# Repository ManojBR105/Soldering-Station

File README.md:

# Soldering-Station
Board and Schematics for Soldering station based on hakko 907 clone. 
Consider there is slight difference in schematic, the buzzer is connected to pin no.D13 of the arduino and the lcd pin connected to the D13th pin is connected to the D11th pin of the arduino. (please change this in the arduino code before uploading OR use the modified code in this repository).
In this layout LCD and Encoder are not on the PCB but are connected using Jumper Connectors which makes the assembling job easier when mounting this circuit into a Project case.
The eagle libraries that I have used for this schematic are also with this files copy them to your eagle library.
THANK YOU.

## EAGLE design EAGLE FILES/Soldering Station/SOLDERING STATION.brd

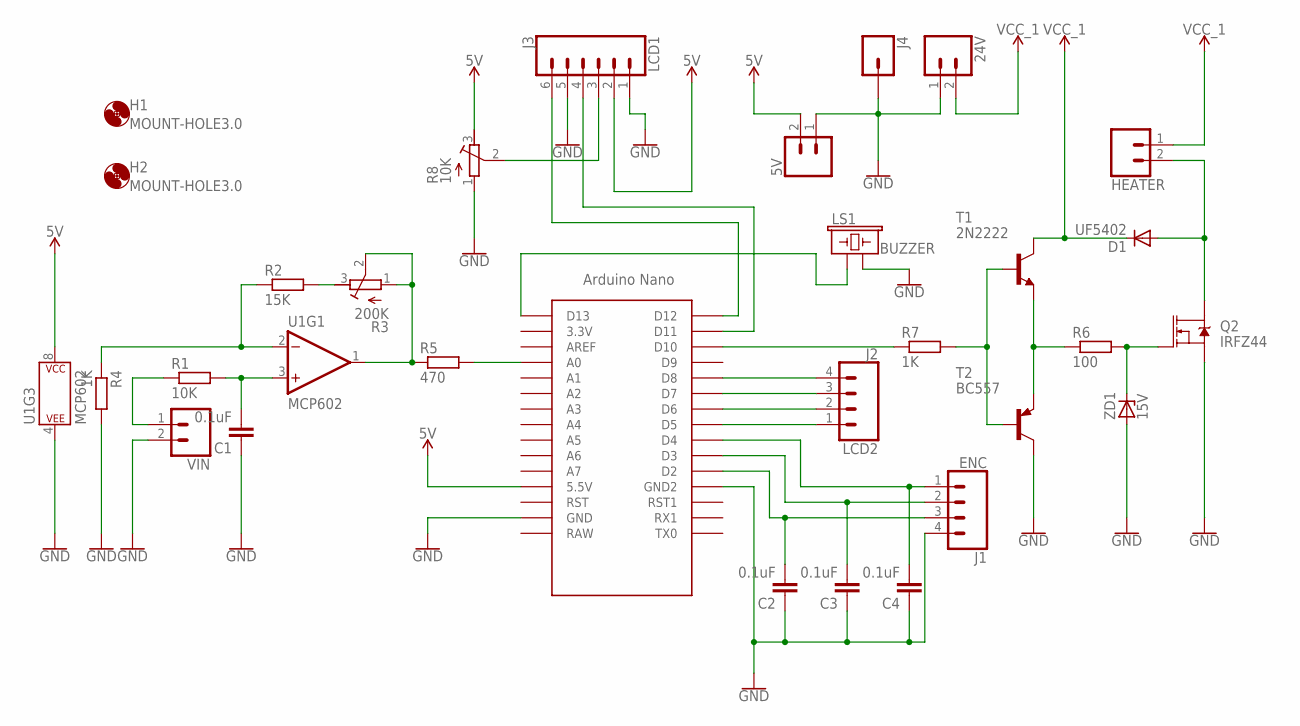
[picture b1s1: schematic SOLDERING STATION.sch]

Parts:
5V, 24V: CONN_025MM; SCREWTERMINAL-5MM-2
C1, C2, C3, C4: 0.1uF; C025-024X044
D1: UF5402; DO41-10
H1, H2: MOUNT-HOLE3.0; 3,0
HEATER: CONN_02PTH4; 1X02_XTRA_BIG
J1: ENC; 1X04_LONGPADS
J2: LCD2; 1X04_LONGPADS
J3: LCD1; 1X06_LONGPADS
J4: CONN_01PTH_2MM; 1X01_2MM
LS1: BUZZER; BUZZER-12MM-NS
Q2: IRFZ44; TO220V
R1: 10K; 0204/7
R2: 15K; 0204/7
R3: 200K; RTRIM64W
R4, R7: 1K; 0204/7
R5: 470; 0204/7
R6: 100; 0204/7
R8: 10K; RTRIM64W
T1: 2N2222; TO92-EBC-OVAL
T2: BC557; TO92
U1: MCP602; DIP08
U$1: NANO
VIN: CONN_02POLAR_LOCK; MOLEX-1X2_LOCK
ZD1: 15V; DO41Z10

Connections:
5V: 5V.2, J3.2, R8.3 (E), U1.8 (P$V+), U$1.5V (5.5V)
GND: 5V.1, 24V.1, C1.1, C2.1, C3.1, C4.1, J1.4, J3.1, J3.5, J4.1, LS1.- (2), Q2.3 (S), R4.2, R8.1 (A), T2.3 (C), U1.4 (P$V-), U$1.GND, U$1.GND1 (GND2), VIN.2, ZD1.A
unnamed: C1.2, R1.2, U1.3 (+IN)
unnamed: R2.1, R4.1, U1.2 (-IN)
unnamed: R1.1, VIN.1
unnamed: R2.2, R3.3 (E)
unnamed: R3.1 (A), R3.2 (S), R5.1, U1.1 (OUT)
unnamed: R5.2, U$1.A0
unnamed: R7.1, U$1.D10
unnamed: D1.A, HEATER.2, Q2.2 (D)
unnamed: C4.2, J1.1, U$1.D4
unnamed: R7.2, T1.B, T2.2 (B)
unnamed: R6.1, T1.E, T2.1 (E)
unnamed: Q2.1 (G), R6.2, ZD1.C
unnamed: C3.2, J1.2, U$1.D3
unnamed: C2.2, J1.3, U$1.D2
unnamed: J2.1, U$1.D5
unnamed: J2.2, U$1.D6
unnamed: J3.3, R8.2 (S)
unnamed: J2.3, U$1.D7
unnamed: J2.4, U$1.D8
unnamed: LS1.+ (1), U$1.D13
unnamed: J3.6, U$1.D12
unnamed: J3.4, U$1.D11
VCC_1: 24V.2, D1.C, HEATER.1, T1.C

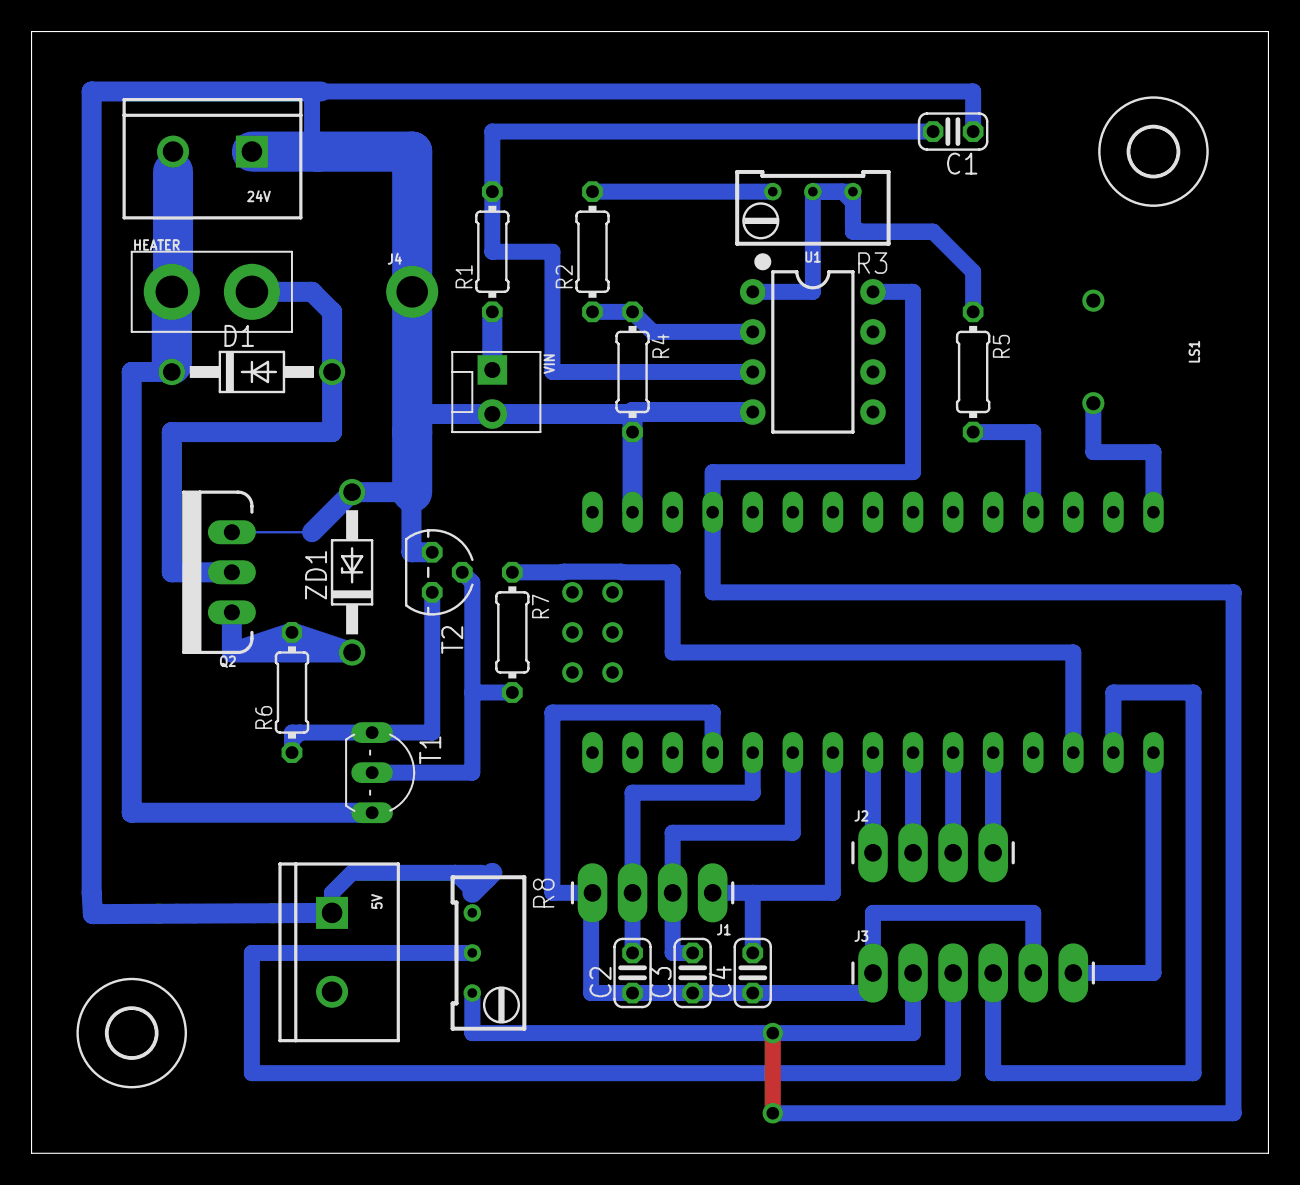
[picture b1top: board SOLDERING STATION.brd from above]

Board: 2 copper layers, 78.4 x 71.1 mm, 30 parts (0 on the bottom side), 25 nets.

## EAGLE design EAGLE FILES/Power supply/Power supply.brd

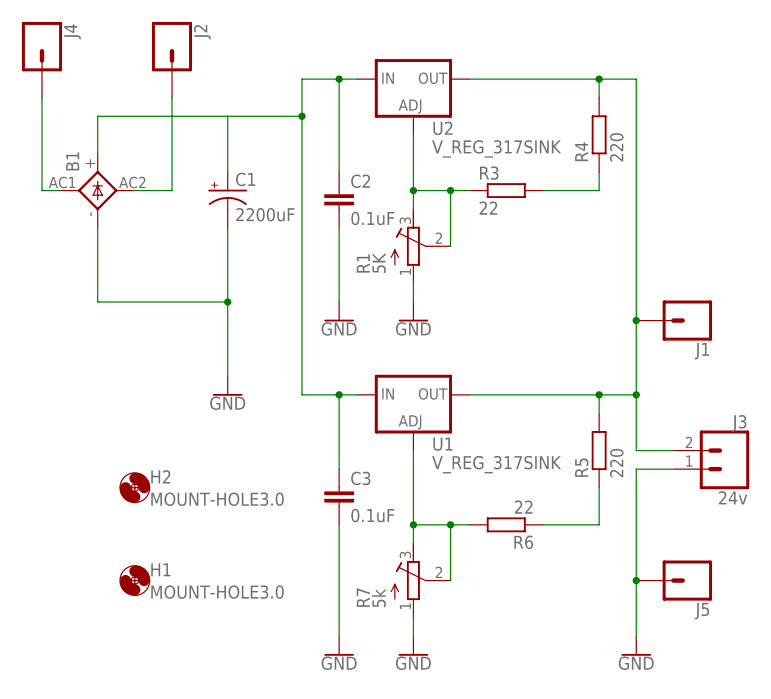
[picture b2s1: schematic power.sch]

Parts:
B1: GBPC1
C1: 2200uF; E7,5-16
C2, C3: 0.1uF; C025-024X044
H1, H2: MOUNT-HOLE3.0; 3,0
J1, J2, J4, J5: CONN_01PTH_2MM; 1X01_2MM
J3: 24v; SCREWTERMINAL-5MM-2
R1: 5K; RTRIM64W
R3, R6: 22; 0207/10
R4, R5: 220; 0207/10
R7: 5k; RTRIM64W
U1, U2: V_REG_317SINK; TO220-ADJ

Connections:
GND: B1.-, C1.-, C2.2, C3.2, J3.1, J5.1, R1.1 (A), R7.1 (A)
unnamed: R1.2 (S), R1.3 (E), R3.1, U2.ADJ
unnamed: B1.AC1, J4.1
unnamed: B1.AC2, J2.1
unnamed: R3.2, R4.1
unnamed: J1.1, J3.2, R4.2, R5.2, U1.OUT, U2.OUT
unnamed: B1.+, C1.+, C2.1, C3.1, U1.IN, U2.IN
unnamed: R6.2, R7.2 (S), R7.3 (E), U1.ADJ
unnamed: R5.1, R6.1

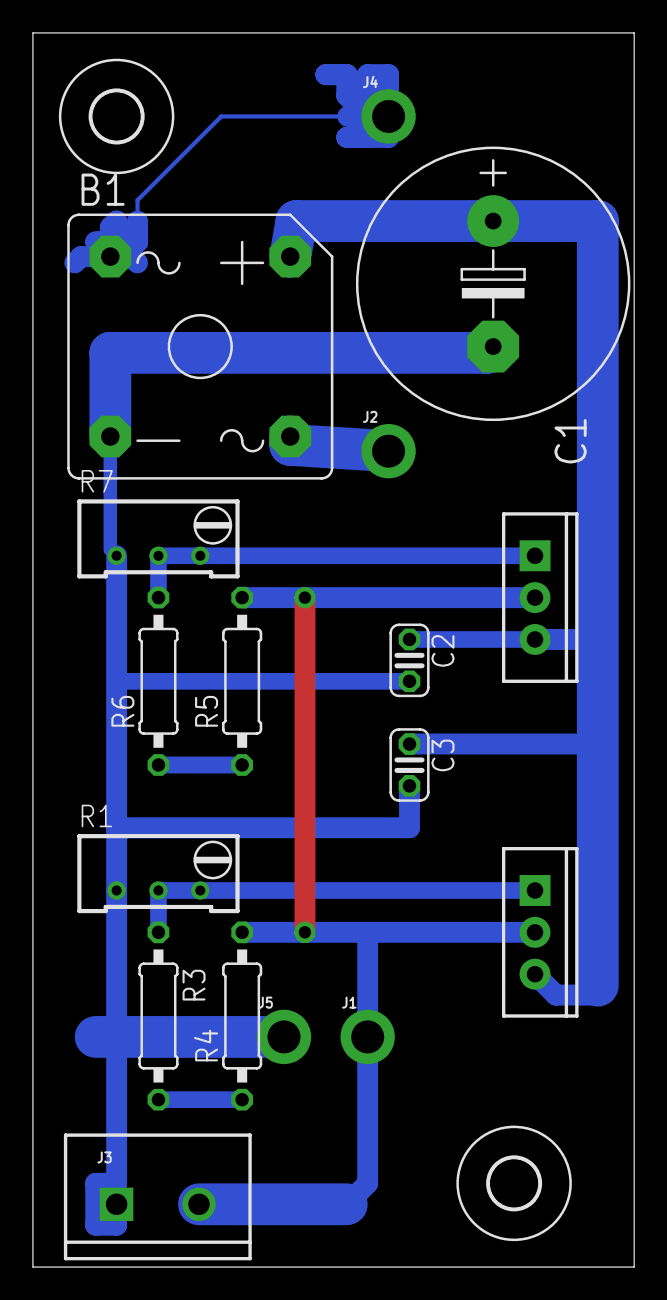
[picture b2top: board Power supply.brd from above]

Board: 2 copper layers, 36.5 x 74.9 mm, 19 parts (0 on the bottom side), 9 nets.

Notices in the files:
parts and their libraries:
SparkFun-Connectors: Licensing: Creative Commons ShareAlike 4.0 International - https://creativecommons.org/licenses/by-sa/4.0
